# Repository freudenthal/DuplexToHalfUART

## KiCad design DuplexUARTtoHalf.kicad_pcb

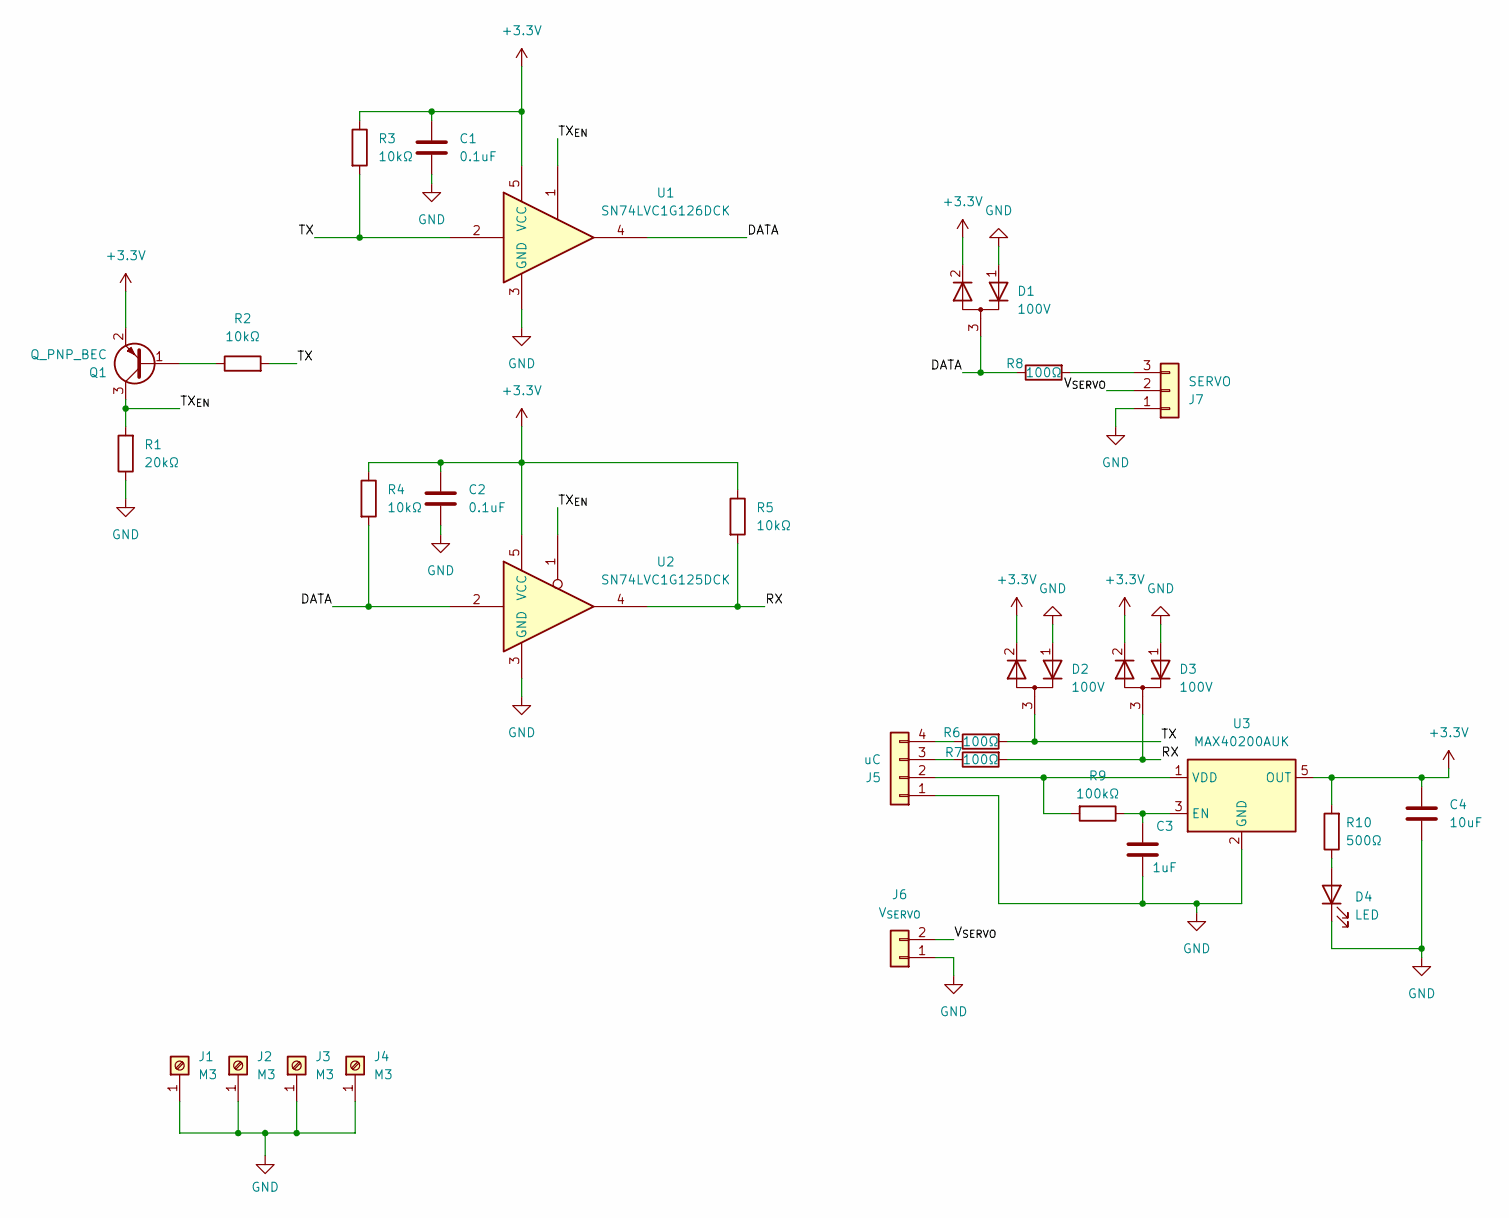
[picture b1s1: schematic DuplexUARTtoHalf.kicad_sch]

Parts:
C1, C2: 0.1uF; C_0805_2012Metric
C3: 1uF; C_0805_2012Metric
C4: 10uF; C_0805_2012Metric
D1, D2, D3: 100V; SOT-23-3
D4: LED; LED_0805_2012Metric
J1, J2, J3, J4: M3; MountingHole_3.2mm_M3_DIN965_Pad
J5: uC; PinHeader_1x04_P2.54mm_Vertical
J6: V_{SERVO}; PinHeader_1x02_P2.54mm_Vertical
J7: SERVO; PinHeader_1x03_P2.54mm_Vertical
Q1: Q_PNP_BEC; SOT-23-3
R1: 20kΩ; R_0805_2012Metric
R2, R3, R4, R5: 10kΩ; R_0805_2012Metric
R6, R7, R8: 100Ω; R_0805_2012Metric
R9: 100kΩ; R_0805_2012Metric
R10: 500Ω; R_0805_2012Metric
U1: SN74LVC1G126DCK; Texas_R-PDSO-G5_DCK-5
U2: SN74LVC1G125DCK; Texas_R-PDSO-G5_DCK-5
U3: MAX40200AUK; SOT-23-5

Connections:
+3.3V: C1.1, C2.1, C4.1, D1.2 (K), D2.2 (K), D3.2 (K), Q1.2 (E), R3.1, R4.1, R5.1, R10.2, U1.5 (VCC), U2.5 (VCC), U3.5 (OUT)
/DATA: D1.3 (A), R4.2, R8.1, U1.4, U2.2
/RX: D3.3 (A), R5.2, R7.2, U2.4
/TX: D2.3 (A), R2.2, R3.2, R6.2, U1.2
/TX_{EN}: Q1.3 (C), R1.2, U1.1, U2.1
/V_{SERVO}: J6.2, J7.2
GND: C1.2, C2.2, C3.2, C4.2, D1.1 (K), D2.1 (K), D3.1 (K), D4.1 (K), J1.1, J2.1, J3.1, J4.1, J5.1, J6.1, J7.1, R1.1, U1.3 (GND), U2.3 (GND), U3.2 (GND)
unnamed: D4.2 (A), R10.1
unnamed: J5.2, R9.2, U3.1 (VDD)
unnamed: J5.3, R7.1
unnamed: J5.4, R6.1
unnamed: J7.3, R8.2
unnamed: Q1.1 (B), R2.1
unnamed: C3.1, R9.1, U3.3 (EN)

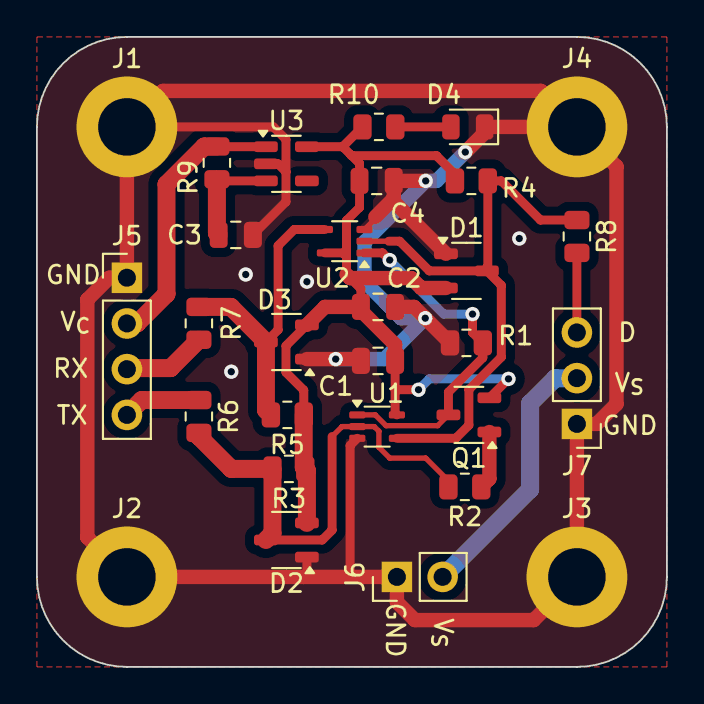
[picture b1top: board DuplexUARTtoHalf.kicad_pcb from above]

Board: 2 copper layers, 35.0 x 35.0 mm, 29 parts (0 on the bottom side), 14 nets.

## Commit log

2024-11-19 Initial commit.
